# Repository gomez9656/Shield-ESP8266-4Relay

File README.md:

# Shield-ESP8266-4Relay
In college, I had the opportunity to work in a design of an IoT system. 

The project was quite simple: mechanics students wanted to use the 3D printers that were in the classroom. from the comfort of their house. It's very usual that they spend hours designing some mechanism in AutoCAD or equivalent, and then they spend hours waiting for the 3D printer to finish the job. To accelerate this process, they wanted to upload the files to the 3D printers and turn on the 3D printers at any given time and start printing, so when they arrive at the classroom the next day, the printing was finished.

My job was to use a relay to control the power for the 3D printers, using the popular ESP8266. So, I designed a PCB shield, that lies between the ESP8266 and a 4 relay board, as you can see in the images, the PCB is quite simple. 
Although the "abstraction" of the PCB was quite hard because I had to think which part is going up/down and in which order. Once done, the PCB design was quite easy. 

The software was made in Arduino IDE using C, and the ESP8266 connected to a dashboard in Ubidots(cloud). Using a button, the user was able to turn on/off the 3D printer.

For the prototype of the board, I use the same process that was explained in my other repository: Excellon_to_Gcode.

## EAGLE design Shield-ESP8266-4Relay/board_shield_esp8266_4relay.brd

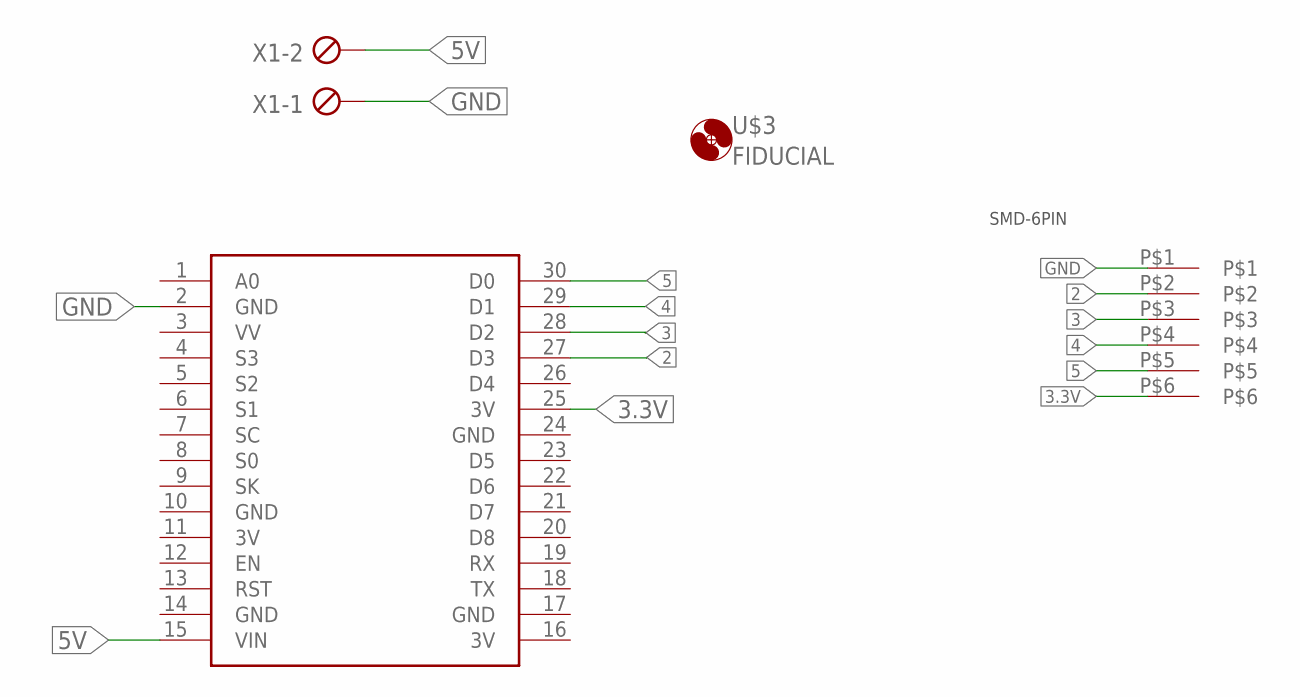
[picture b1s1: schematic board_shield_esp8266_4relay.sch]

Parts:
U$1: 6_PIN_HEADER_SMD_FEMALE
U$2: NODEMCU
U$3: FIDUCIAL; ROLAND_1
X1: MKDS1/2-3,81; 2POL381

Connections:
2: U$1.P$2, U$2.27 (D3)
3: U$1.P$3, U$2.28 (D2)
3.3V: U$1.P$6, U$2.25 (3V)
3V: U$2.11 (3V), U$2.16 (3V)
4: U$1.P$4, U$2.29 (D1)
5: U$1.P$5, U$2.30 (D0)
5V: U$2.15 (VIN), X1.2
GND: U$1.P$1, U$2.2 (GND), U$2.10 (GND), U$2.14 (GND), U$2.17 (GND), U$2.24 (GND), X1.1

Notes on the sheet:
SMD-6PIN

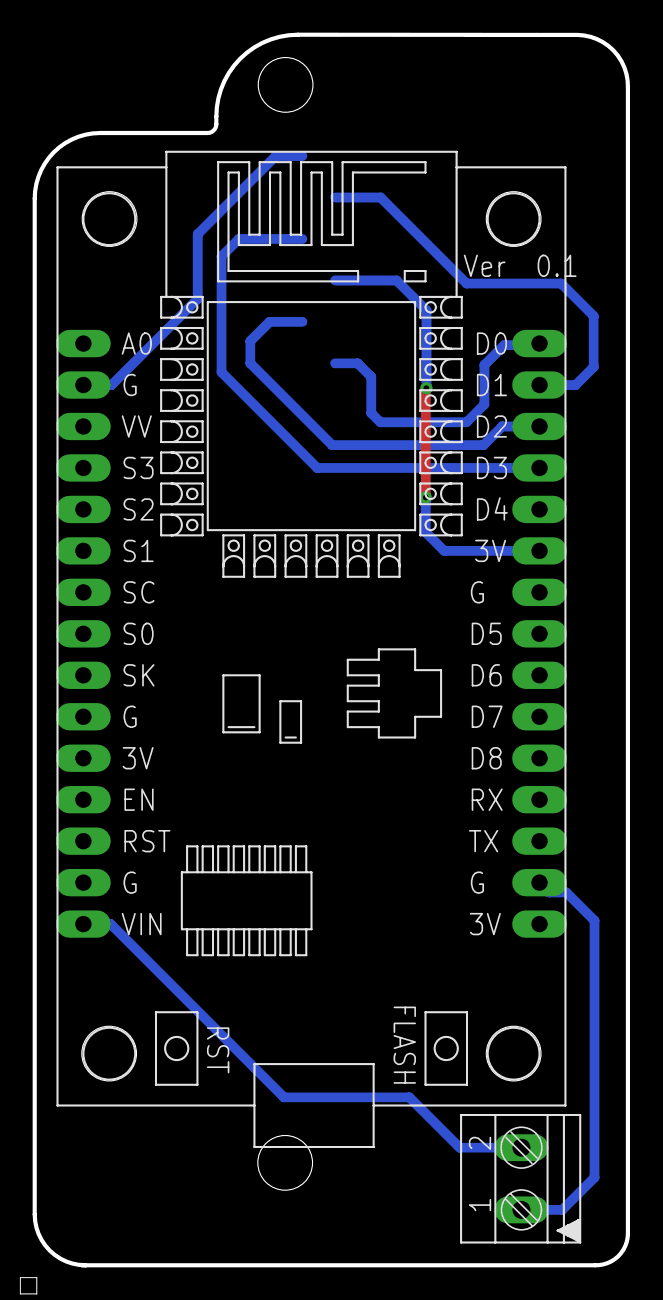
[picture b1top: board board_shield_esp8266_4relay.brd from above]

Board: 2 copper layers, 36.3 x 75.4 mm, 4 parts (1 on the bottom side), 8 nets.
